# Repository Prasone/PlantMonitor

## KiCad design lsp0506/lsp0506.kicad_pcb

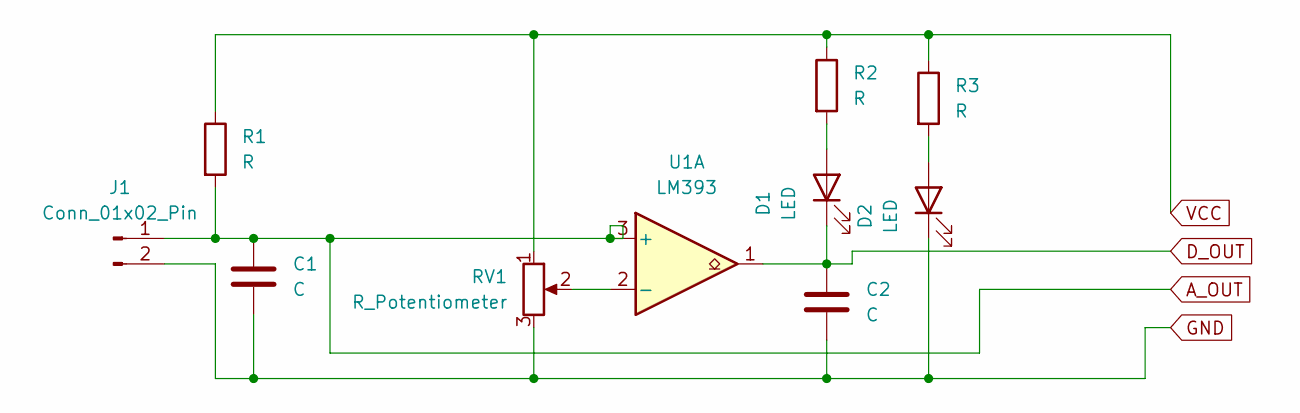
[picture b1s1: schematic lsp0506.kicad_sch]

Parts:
C1, C2: C; CP_Axial_L11.0mm_D5.0mm_P18.00mm_Horizontal
D1, D2: LED; LED_D2.0mm_W4.0mm_H2.8mm_FlatTop
J1: Conn_01x02_Pin; PinHeader_1x02_P1.00mm_Horizontal
R1, R2, R3: R; R_Axial_DIN0204_L3.6mm_D1.6mm_P7.62mm_Horizontal
RV1: R_Potentiometer; Potentiometer_Bourns_3266P_Horizontal
U1: LM393; DIP-8_W7.62mm

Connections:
A_OUT: C1.1, J1.1, R1.2, U1.3 (+)
D_OUT: C2.1, D1.1 (K), U1.1
GND: C1.2, C2.2, D2.1 (K), J1.2, RV1.3
unnamed: D1.2 (A), R2.2
unnamed: D2.2 (A), R3.2
unnamed: RV1.2, U1.2 (-)
VCC: R1.1, R2.1, R3.1, RV1.1

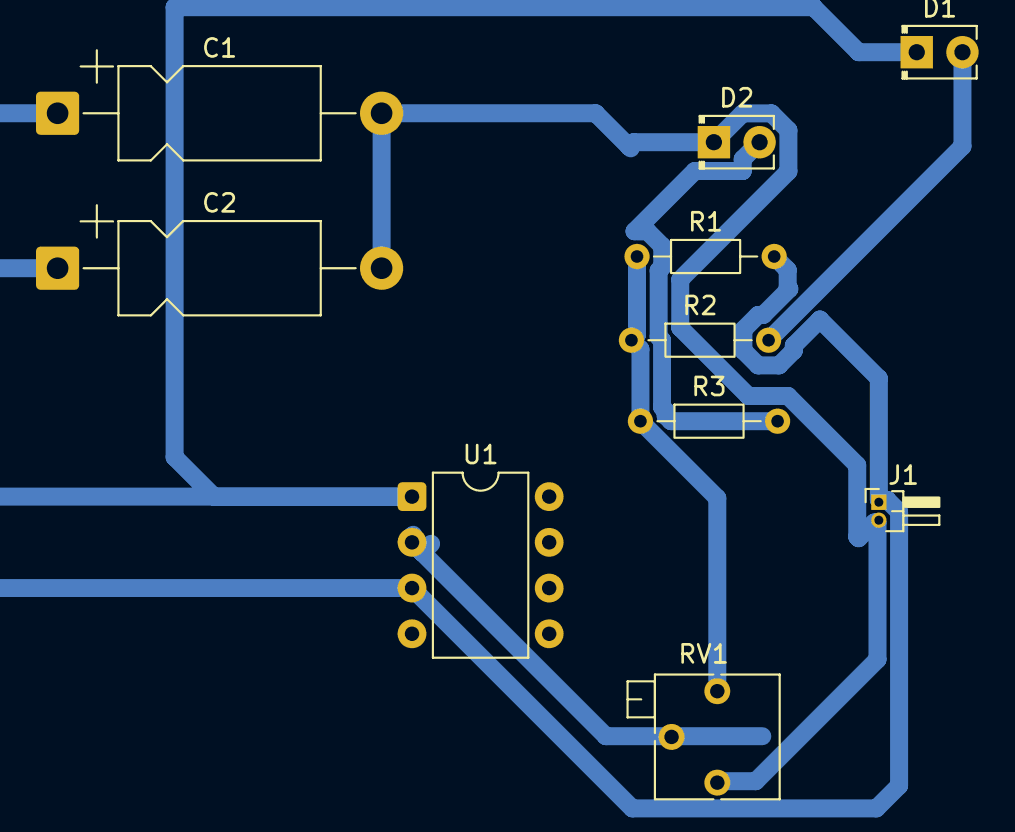
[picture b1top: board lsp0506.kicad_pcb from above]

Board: 2 copper layers, 10 parts (0 on the bottom side), 7 nets.
